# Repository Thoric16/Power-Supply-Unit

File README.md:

# Intelligent Power Distribution Unit (PSU) for Robotic Systems

A custom-designed, high-reliability Power Supply Unit (PSU) engineered to act as the centralized power management hub and hardware safety backbone for an advanced robotics platform. This board safely bridges high-draw actuator systems with sensitive compute electronics, featuring real-time telemetry and integrated fault protection.

---

## 🚀 Core Engineering Features

* **Centralized Voltage Regulation:** Features onboard step-down (buck) converters engineered to deliver clean, highly stable regulated voltage rails dedicated to sensitive compute units and sensor payloads.
* **Dynamic Power Routing:** Implements remotely switchable outputs, enabling upstream software to dynamically toggle power rails on-the-fly to conserve system energy or reset frozen peripherals.
* **Real-Time Current Monitoring:** Integrates inline current sensing architectures across critical nodes to detect electrical deviations, preventing overcurrent conditions from damaging hardware.
* **Hardware-Level Safety Architecture:** Interfaces natively with a physical Emergency Stop (E-Stop) loop, ensuring instantaneous, hardware-level power severance to high-draw chassis drivetrains and robotic arm actuators without relying on software loops.

---

## 🛠️ Technical Design & Specifications

### Hardware Breakdown
* **EDA Tooling:** Designed and routed entirely using KiCad.
* **Target Load Rails:** Dual-domain architecture isolating high-noise inductive motor spikes from digital logic logic rails.
* **Safety Controls:** Low-latency hardware isolation circuit mapped to the master system E-Stop button.

### Target Subsystem Map

| Managed Output Domain | Power Characteristic | Safety / Control Mechanism |
| :--- | :---: | :--- |
| **Compute Payloads** | Stable, Low-Noise Regulated | Upstream Overcurrent Monitored |
| **Sensor Electronics** | High-Precision Filtered | Soft-Switch Controlled |
| **Chassis Drivetrain** | High-Draw / Unregulated | Instantaneous Hardware E-Stop Cutoff |
| **Robotic Arm Drives** | High-Draw / Unregulated | Instantaneous Hardware E-Stop Cutoff |

---

## 💻 Hardware Layout & Physical Assembly

### Manufacturing & Routing Strategy
The PCB layout utilizes broad power planes and deliberate copper pours to handle high-current distribution safely while maintaining a tight, compact form factor. Signal lines for telemetry monitoring are physically isolated away from high-switching buck regulators to mitigate electromagnetic interference (EMI).

### Assembled Module View
Below is the physical validation of the manufactured and populated PSU PCB assembly:

---

## 📁 Repository Navigation Guide

* `/hardware`: Contains the complete source schematic (`.kicad_sch`) and multi-layer board layout files (`.kicad_pcb`).
* `/assets`: High-resolution photographs.

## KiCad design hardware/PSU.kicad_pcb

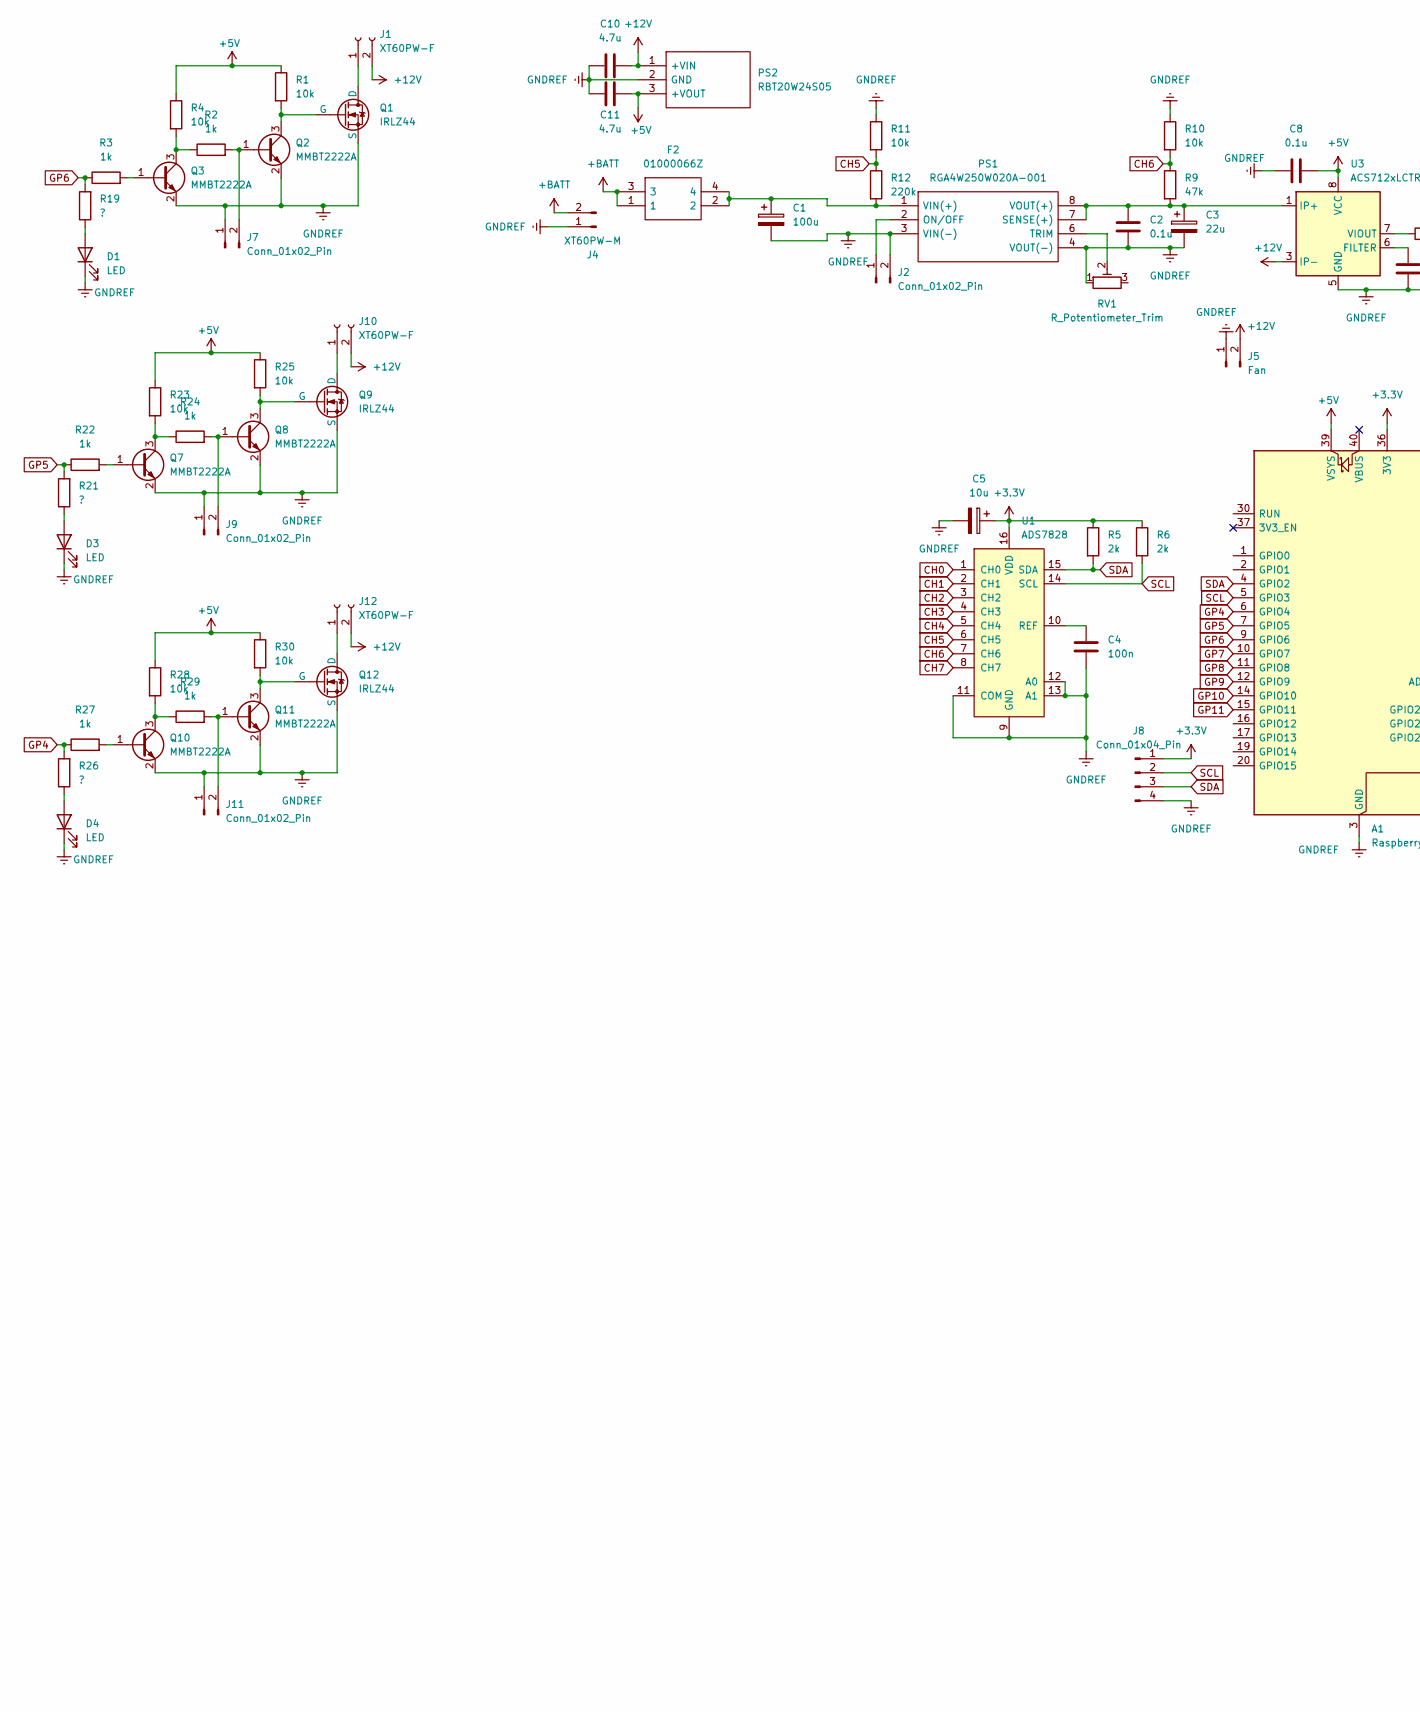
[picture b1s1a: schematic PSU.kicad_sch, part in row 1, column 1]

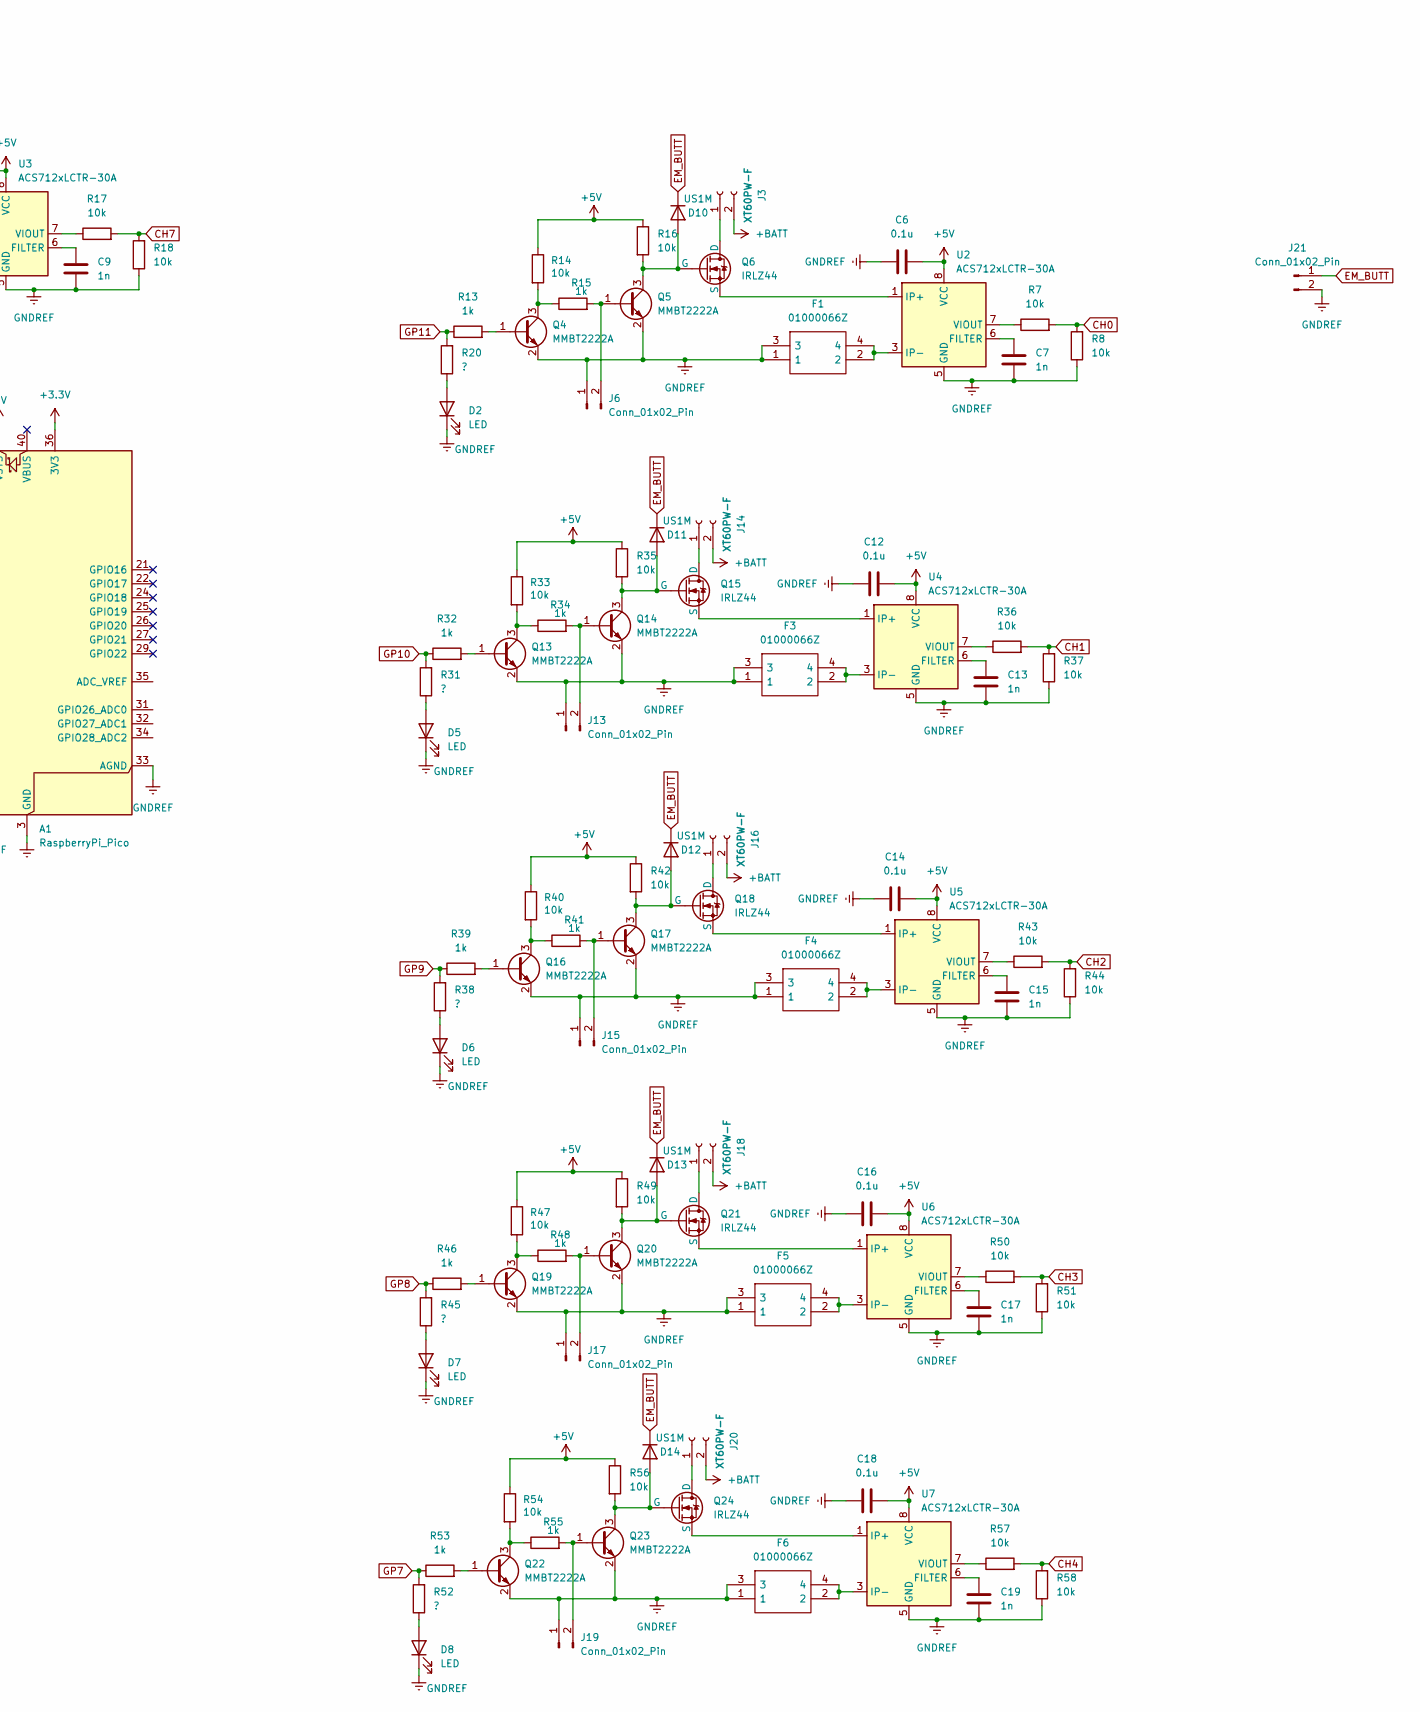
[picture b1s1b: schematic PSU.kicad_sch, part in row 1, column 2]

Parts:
A1: RaspberryPi_Pico; RaspberryPi_Pico_Common_THT
C1: 100u; CP_Elec_10x10.5
C2, C6, C8, C12, C14, C16, C18: 0.1u; C_0603_1608Metric
C3: 22u; CP_Elec_8x6.2
C4: 100n; C_0603_1608Metric
C5: 10u; C_0603_1608Metric
C7, C9, C13, C15, C17, C19: 1n; C_0603_1608Metric
C10, C11: 4.7u; C_0603_1608Metric
D1, D2, D3, D4, D5, D6, D7, D8: LED; LED_0603_1608Metric
D10, D11, D12, D13, D14: US1M; D_SMA
F1, F2, F3, F4, F5, F6: 01000066Z; Mouser Part Number 576-01000066Z
J1, J3, J10, J12, J14, J16, J18, J20: XT60PW-F; AMASS_XT60PW-F_1x02_P7.20mm_Horizontal
J2, J6, J7, J9, J11, J13, J15, J17, J19, J21: Conn_01x02_Pin; PinSocket_1x02_P2.54mm_Vertical
J4: XT60PW-M; AMASS_XT60PW-M_1x02_P7.20mm_Horizontal
J5: Fan; PinSocket_1x02_P2.54mm_Vertical
J8: Conn_01x04_Pin; PinHeader_1x04_P2.54mm_Vertical
PS1: RGA4W250W020A-001; RGA4W250W020A001; Mouser Part Number 967-RGA4W250W020A001
PS2: RBT20W24S05; Manufacturer_Part_Number RBT20W24S05
Q1, Q6, Q9, Q12, Q15, Q18, Q21, Q24: IRLZ44; TO-220-3_Vertical_custom
Q2, Q3, Q4, Q5, Q7, Q8, Q10, Q11, Q13, Q14, Q16, Q17, Q19, Q20, Q22, Q23: MMBT2222A; SOT-23
R1, R4, R7, R8, R10, R11, R14, R16, R17, R18, R23, R25, R28, R30, R33, R35, R36, R37, R40, R42, R43, R44, R47, R49, R50, R51, R54, R56, R57, R58: 10k; R_0603_1608Metric
R2, R3, R13, R15, R22, R24, R27, R29, R32, R34, R39, R41, R46, R48, R53, R55: 1k; R_0603_1608Metric
R5, R6: 2k; R_0603_1608Metric
R9: 47k; R_0603_1608Metric
R12: 220k; R_0603_1608Metric
R19, R20, R21, R26, R31, R38, R45, R52: ?; R_0603_1608Metric
RV1: R_Potentiometer_Trim; Potentiometer_Bourns_3296W_Vertical
U1: ADS7828; TSSOP-16_4.4x5mm_P0.65mm
U2, U3, U4, U5, U6, U7: ACS712xLCTR-30A; SOIC-8_3.9x4.9mm_P1.27mm

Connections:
+3.3V: A1.36 (3V3), C5.1, J8.1, R5.1, R6.1, U1.16 (VDD)
+5V: A1.39 (VSYS), C6.2, C8.2, C11.2, C12.2, C14.2, C16.2, C18.2, PS2.3 (+VOUT), R1.1, R4.1, R14.1, R16.1, R23.1, R25.1, R28.1, R30.1, R33.1, R35.1, R40.1, R42.1, R47.1, R49.1, R54.1, R56.1, U2.8 (VCC), U3.8 (VCC), U4.8 (VCC), U5.8 (VCC), U6.8 (VCC), U7.8 (VCC)
+12V: C10.2, J1.2, J5.2, J10.2, J12.2, PS2.1 (+VIN), U3.3 (IP-), U3.4 (IP-)
+BATT: F2.1, F2.3, J3.2, J4.2, J14.2, J16.2, J18.2, J20.2
CH0: R7.2, R8.2, U1.1 (CH0)
CH1: R36.2, R37.2, U1.2 (CH1)
CH2: R43.2, R44.2, U1.3 (CH2)
CH3: R50.2, R51.2, U1.4 (CH3)
CH4: R57.2, R58.2, U1.5 (CH4)
CH5: R11.2, R12.1, U1.6 (CH5)
CH6: R9.1, R10.2, U1.7 (CH6)
CH7: R17.2, R18.2, U1.8 (CH7)
EM_BUTT: D10.1 (K), D11.1 (K), D12.1 (K), D13.1 (K), D14.1 (K), J21.1
GNDREF: A1.3 (GND), A1.8 (GND), A1.13 (GND), A1.18 (GND), A1.23 (GND), A1.28 (GND), A1.33 (AGND), A1.38 (GND), C1.2, C2.2, C3.2, C4.2, C5.2, C6.1, C7.1, C8.1, C9.1, C10.1, C11.1, C12.1, C13.1, C14.1, C15.1, C16.1, C17.1, C18.1, C19.1, D1.1 (K), D2.1 (K), D3.1 (K), D4.1 (K), D5.1 (K), D6.1 (K), D7.1 (K), D8.1 (K), F1.1, F1.3, F3.1, F3.3, F4.1, F4.3, F5.1, F5.3, F6.1, F6.3, J2.2, J4.1, J5.1, J6.1, J7.1, J8.4, J9.1, J11.1, J13.1, J15.1, J17.1, J19.1, J21.2, PS1.3 (VIN(-)), PS1.4 (VOUT(-)), PS2.2 (GND), Q1.3 (S), Q2.2 (E), Q3.2 (E), Q4.2 (E), Q5.2 (E), Q7.2 (E), Q8.2 (E), Q9.3 (S), Q10.2 (E), Q11.2 (E), Q12.3 (S), Q13.2 (E), Q14.2 (E), Q16.2 (E), Q17.2 (E), Q19.2 (E), Q20.2 (E), Q22.2 (E), Q23.2 (E), R8.1, R10.1, R11.1, R18.1, R37.1, R44.1, R51.1, R58.1, RV1.1, U1.9 (GND), U1.11 (COM), U1.12 (A0), U1.13 (A1), U2.5 (GND), U3.5 (GND), U4.5 (GND), U5.5 (GND), U6.5 (GND), U7.5 (GND)
GP4: A1.6 (GPIO4), R26.2, R27.1
GP5: A1.7 (GPIO5), R21.2, R22.1
GP6: A1.9 (GPIO6), R3.1, R19.2
GP7: A1.10 (GPIO7), R52.2, R53.1
GP8: A1.11 (GPIO8), R45.2, R46.1
GP9: A1.12 (GPIO9), R38.2, R39.1
GP10: A1.14 (GPIO10), R31.2, R32.1
GP11: A1.15 (GPIO11), R13.1, R20.2
unnamed: D1.2 (A), R19.1
unnamed: D2.2 (A), R20.1
unnamed: D3.2 (A), R21.1
unnamed: D4.2 (A), R26.1
unnamed: D5.2 (A), R31.1
unnamed: D6.2 (A), R38.1
unnamed: D7.2 (A), R45.1
unnamed: D8.2 (A), R52.1
unnamed: D10.2 (A), Q5.3 (C), Q6.2 (G), R16.2
unnamed: D11.2 (A), Q14.3 (C), Q15.2 (G), R35.2
unnamed: D12.2 (A), Q17.3 (C), Q18.2 (G), R42.2
unnamed: D13.2 (A), Q20.3 (C), Q21.2 (G), R49.2
unnamed: D14.2 (A), Q23.3 (C), Q24.2 (G), R56.2
unnamed: F1.2, F1.4, U2.3 (IP-), U2.4 (IP-)
unnamed: F3.2, F3.4, U4.3 (IP-), U4.4 (IP-)
unnamed: F4.2, F4.4, U5.3 (IP-), U5.4 (IP-)
unnamed: F5.2, F5.4, U6.3 (IP-), U6.4 (IP-)
unnamed: F6.2, F6.4, U7.3 (IP-), U7.4 (IP-)
unnamed: J1.1, Q1.1 (D)
unnamed: J2.1, PS1.2 (ON/OFF)
unnamed: J3.1, Q6.1 (D)
unnamed: J6.2, Q5.1 (B), R15.2
unnamed: J7.2, Q2.1 (B), R2.2
unnamed: J9.2, Q8.1 (B), R24.2
unnamed: J10.1, Q9.1 (D)
unnamed: J11.2, Q11.1 (B), R29.2
unnamed: J12.1, Q12.1 (D)
unnamed: J13.2, Q14.1 (B), R34.2
unnamed: J14.1, Q15.1 (D)
unnamed: J15.2, Q17.1 (B), R41.2
unnamed: J16.1, Q18.1 (D)
unnamed: J17.2, Q20.1 (B), R48.2
unnamed: J18.1, Q21.1 (D)
unnamed: J19.2, Q23.1 (B), R55.2
unnamed: J20.1, Q24.1 (D)
unnamed: C2.1, C3.1, PS1.7 (SENSE(+)), PS1.8 (VOUT(+)), R9.2, U3.1 (IP+), U3.2 (IP+)
unnamed: PS1.6 (TRIM), RV1.2
unnamed: C1.1, F2.2, F2.4, PS1.1 (VIN(+)), R12.2
unnamed: Q1.2 (G), Q2.3 (C), R1.2
unnamed: Q3.1 (B), R3.2
unnamed: Q3.3 (C), R2.1, R4.2
unnamed: Q4.1 (B), R13.2
unnamed: Q4.3 (C), R14.2, R15.1
unnamed: Q6.3 (S), U2.1 (IP+), U2.2 (IP+)
unnamed: Q7.1 (B), R22.2
unnamed: Q7.3 (C), R23.2, R24.1
unnamed: Q8.3 (C), Q9.2 (G), R25.2
unnamed: Q10.1 (B), R27.2
unnamed: Q10.3 (C), R28.2, R29.1
unnamed: Q11.3 (C), Q12.2 (G), R30.2
unnamed: Q13.1 (B), R32.2
unnamed: Q13.3 (C), R33.2, R34.1
unnamed: Q15.3 (S), U4.1 (IP+), U4.2 (IP+)
unnamed: Q16.1 (B), R39.2
unnamed: Q16.3 (C), R40.2, R41.1
unnamed: Q18.3 (S), U5.1 (IP+), U5.2 (IP+)
unnamed: Q19.1 (B), R46.2
unnamed: Q19.3 (C), R47.2, R48.1
unnamed: Q21.3 (S), U6.1 (IP+), U6.2 (IP+)
unnamed: Q22.1 (B), R53.2
unnamed: Q22.3 (C), R54.2, R55.1
unnamed: Q24.3 (S), U7.1 (IP+), U7.2 (IP+)
unnamed: C4.1, U1.10 (REF)
unnamed: C7.2, U2.6 (FILTER)
unnamed: R7.1, U2.7 (VIOUT)
unnamed: C9.2, U3.6 (FILTER)
unnamed: R17.1, U3.7 (VIOUT)
unnamed: C13.2, U4.6 (FILTER)
unnamed: R36.1, U4.7 (VIOUT)
unnamed: C15.2, U5.6 (FILTER)
unnamed: R43.1, U5.7 (VIOUT)
unnamed: C17.2, U6.6 (FILTER)
unnamed: R50.1, U6.7 (VIOUT)
unnamed: C19.2, U7.6 (FILTER)
unnamed: R57.1, U7.7 (VIOUT)
SCL: A1.5 (GPIO3), J8.2, R6.2, U1.14 (SCL)
SDA: A1.4 (GPIO2), J8.3, R5.2, U1.15 (SDA)

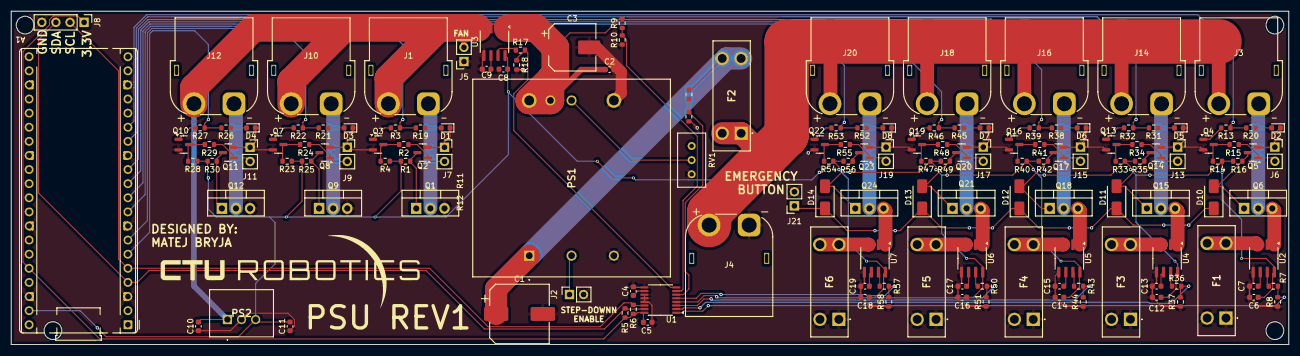
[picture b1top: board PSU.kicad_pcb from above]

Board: 4 copper layers, 230.0 x 60.0 mm, 152 parts (0 on the bottom side), 99 nets.

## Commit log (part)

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2026-06-22 Revise README for Intelligent Power Distribution Unit
    Expanded the README to provide detailed information about the Intelligent Power Distribution Unit, including core features, technical specifications, and repository navigation.
2026-06-22 added folders
2026-06-23 Remove duplicate image from README
    Removed duplicate image from the README.
